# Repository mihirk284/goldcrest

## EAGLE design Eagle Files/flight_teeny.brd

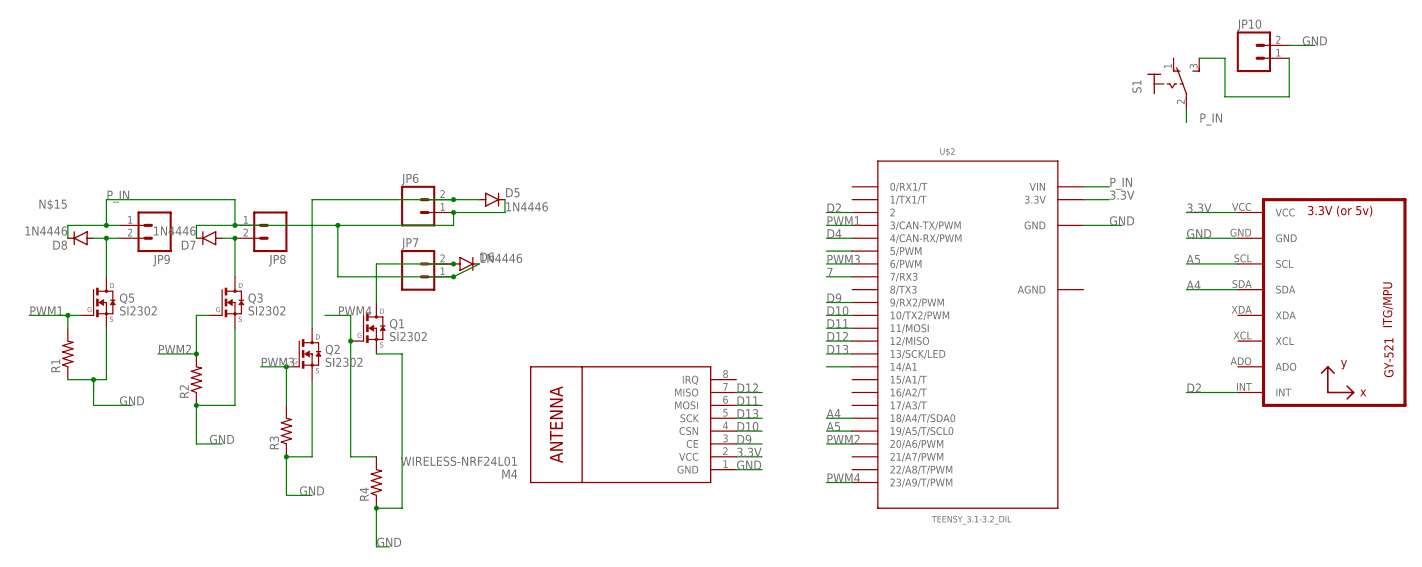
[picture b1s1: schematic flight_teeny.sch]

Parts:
D5, D6, D7, D8: 1N4446; DO35-10
JP6, JP7, JP8, JP9: M021X02_NO_SILK; 1X02_NO_SILK
JP10: M02PTH; 1X02
M4: WIRELESS-NRF24L01
Q1, Q2, Q3, Q5: SI2302; SOT23
R1, R2, R3, R4: RESISTORAXIAL-0.3; AXIAL-0.3
S1: M9040P
U2: GY-521MPU6050; GY-521
U$2: TEENSY_3.1-3.2_DIL; TEENSY_3.0-3.2&LC_DIL

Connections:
3.3V: M4.2 (VCC), U2.VCC, U$2.3.3V
7: U$2.7 (7/RX3)
A4: U2.SDA, U$2.18/A4 (18/A4/T/SDA0)
A5: U2.SCL, U$2.19/A5 (19/A5/T/SCL0)
AGND: U$2.AGND
D2: U2.INT, U$2.2
D4: U$2.4 (4/CAN-RX/PWM)
D9: M4.3 (CE), U$2.9 (9/RX2/PWM)
D10: M4.4 (CSN), U$2.10 (10/TX2/PWM)
D11: M4.6 (MOSI), U$2.11 (11/MOSI)
D12: M4.7 (MISO), U$2.12 (12/MISO)
D13: M4.5 (SCK), U$2.13 (13/SCK/LED)
GND: JP10.2, M4.1 (GND), Q1.2 (S), Q2.2 (S), Q3.2 (S), Q5.2 (S), R1.P$1 (1), R2.P$1 (1), R3.P$1 (1), R4.P$1 (1), U2.GND, U$2.GND
unnamed: D6.A, JP7.2, Q1.3 (D)
unnamed: D8.A, JP9.2, Q5.3 (D)
unnamed: D5.A, JP6.2, Q2.3 (D)
unnamed: D7.A, JP8.2, Q3.3 (D)
unnamed: JP10.1, S1.3 (S)
PWM1: Q5.1 (G), R1.P$2 (2), U$2.3 (3/CAN-TX/PWM)
PWM2: Q3.1 (G), R2.P$2 (2), U$2.20/A6 (20/A6/PWM)
PWM3: Q2.1 (G), R3.P$2 (2), U$2.6 (6/PWM)
PWM4: Q1.1 (G), R4.P$2 (2), U$2.23/A9 (23/A9/T/PWM)
P_IN: D5.C, D6.C, D7.C, D8.C, JP6.1, JP7.1, JP8.1, JP9.1, S1.2, U$2.VIN

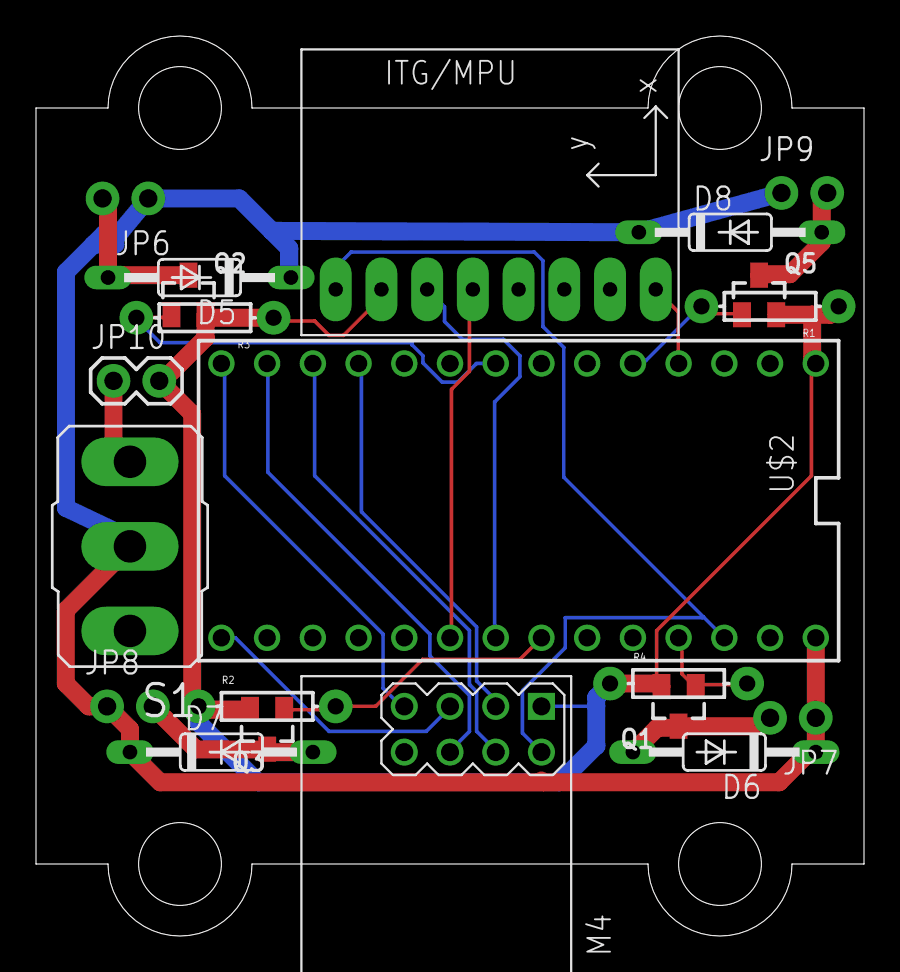
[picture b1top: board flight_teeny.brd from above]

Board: 2 copper layers, 46.0 x 50.0 mm, 21 parts (0 on the bottom side), 20 nets.

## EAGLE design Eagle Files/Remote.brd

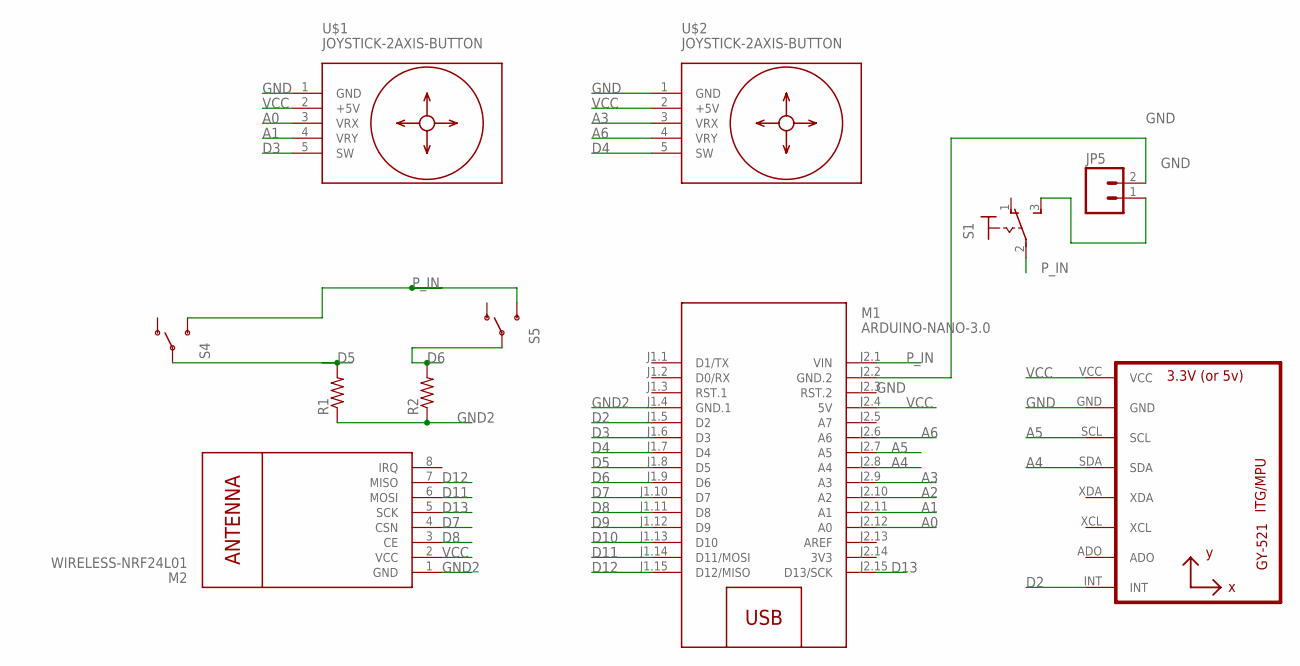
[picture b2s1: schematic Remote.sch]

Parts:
JP5: M02PTH; 1X02
M1: ARDUINO-NANO-3.0
M2: WIRELESS-NRF24L01
R1, R2: RESISTORAXIAL-0.3; AXIAL-0.3
S1: M9040P
S4, S5: SWITCH-SPSTPTH; SWITCH-SPDT
U1: GY-521MPU6050; GY-521
U$1, U$2: JOYSTICK-2AXIS-BUTTON

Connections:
3V3: M1.J2.14 (3V3)
A0: M1.J2.12 (A0), U$1.3 (VRX)
A1: M1.J2.11 (A1), U$1.4 (VRY)
A2: M1.J2.10 (A2)
A3: M1.J2.9 (A3), U$2.3 (VRX)
A4: M1.J2.8 (A4), U1.SDA
A5: M1.J2.7 (A5), U1.SCL
A6: M1.J2.6 (A6), U$2.4 (VRY)
D2: M1.J1.5 (D2), U1.INT
D3: M1.J1.6 (D3), U$1.5 (SW)
D4: M1.J1.7 (D4), U$2.5 (SW)
D5: M1.J1.8 (D5), R1.P$2 (2), S4.2
D6: M1.J1.9 (D6), R2.P$2 (2), S5.2
D7: M1.J1.10 (D7), M2.4 (CSN)
D8: M1.J1.11 (D8), M2.3 (CE)
D9: M1.J1.12 (D9)
D10: M1.J1.13 (D10)
D11: M1.J1.14 (D11/MOSI), M2.6 (MOSI)
D12: M1.J1.15 (D12/MISO), M2.7 (MISO)
D13: M1.J2.15 (D13/SCK), M2.5 (SCK)
GND: JP5.2, M1.J2.2 (GND.2), U1.GND, U$1.1 (GND), U$2.1 (GND)
GND2: M1.J1.4 (GND.1), M2.1 (GND), R1.P$1 (1), R2.P$1 (1)
unnamed: JP5.1, S1.3 (S)
P_IN: M1.J2.1 (VIN), S1.2, S4.3 (S), S5.3 (S)
VCC: M1.J2.4 (5V), M2.2 (VCC), U1.VCC, U$1.2 (+5V), U$2.2 (+5V)

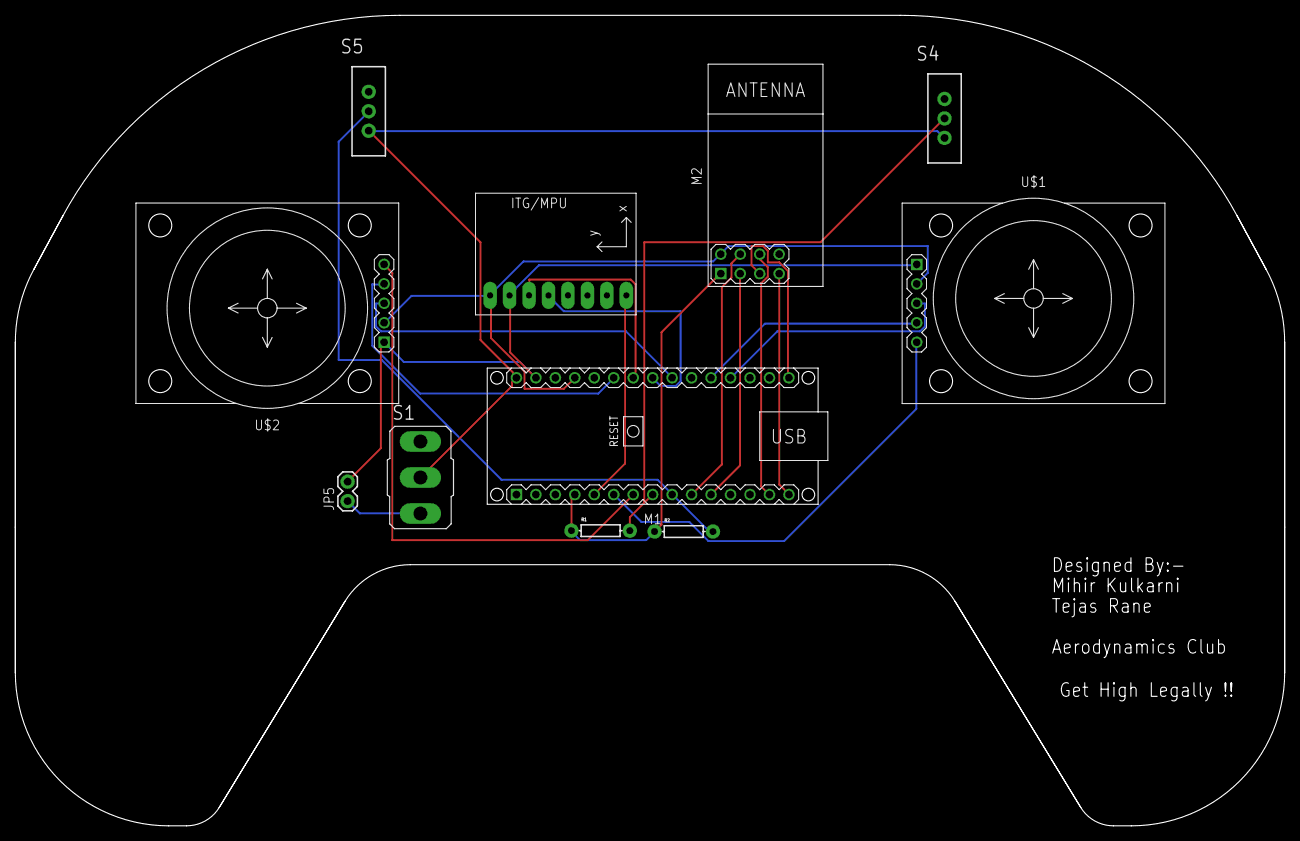
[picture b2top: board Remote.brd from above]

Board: 2 copper layers, 165.6 x 105.8 mm, 11 parts (0 on the bottom side), 21 nets.

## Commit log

2019-05-22 with PID
2019-05-24 Updated Code for Combo and TX2.0
2019-05-25 PCB Files added
2019-05-25 Remote PCB Files added
2019-05-25 first from dharmadhikari
2019-05-28 Final
2020-02-10 Added Teensy Schematic and Board
2020-02-17 Changed power supply for mrf and mpu. Corrected of overlaping pads
2020-02-18 PWM pin corrected. Shifted from 7 to 6
2020-02-21 Added holes
2020-02-22 PCB Shape Added
2020-02-22 Added Shape and Silkscreen
2020-03-06 Added Teensy Code

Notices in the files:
parts and their libraries:
SparkFun: Licensing: CC v3.0 Share-Alike You are welcome to use this library for commercial purposes.
diy-modules: Released under the Creative Commons Attribution 4.0 International License: http://creativecommons.org/licenses/by/4.0
